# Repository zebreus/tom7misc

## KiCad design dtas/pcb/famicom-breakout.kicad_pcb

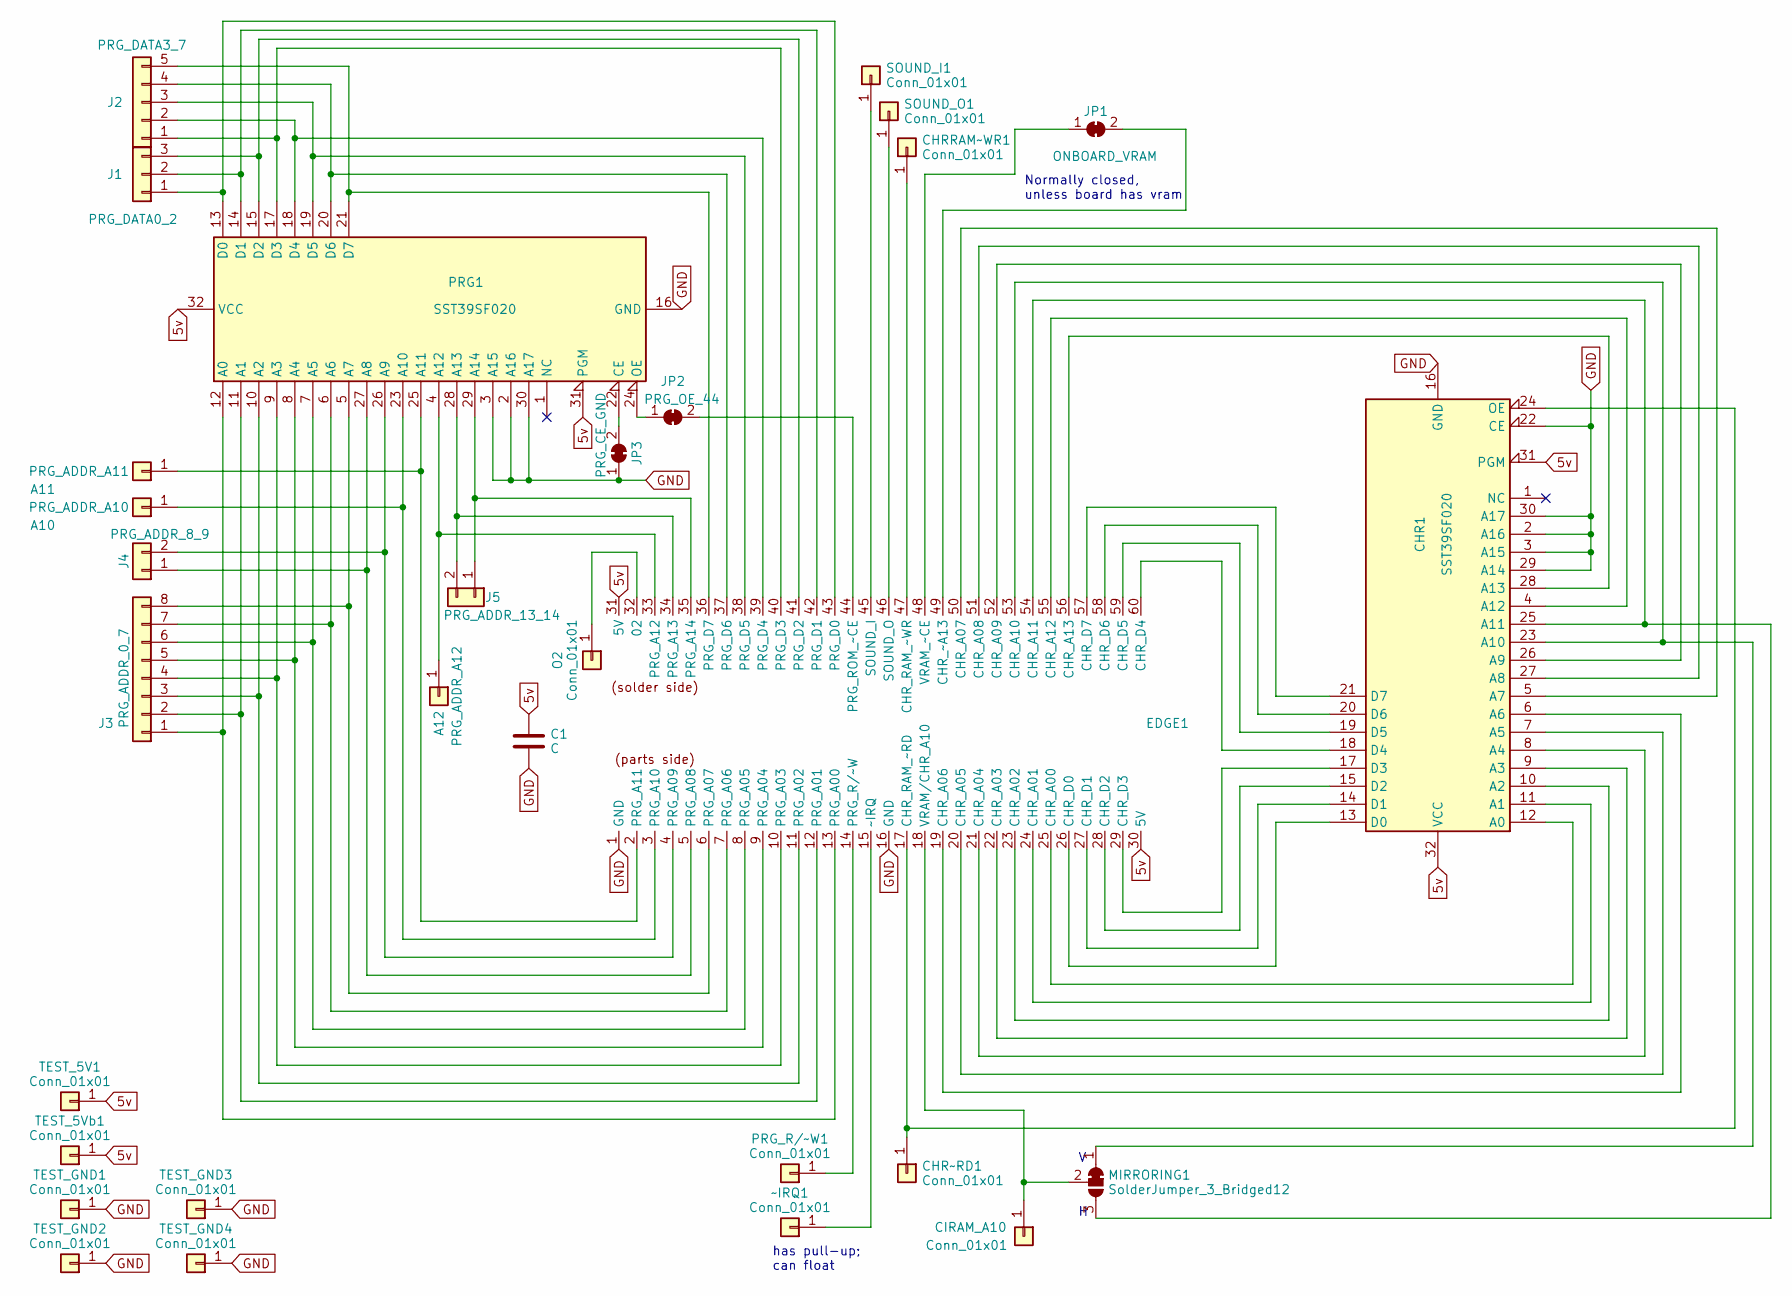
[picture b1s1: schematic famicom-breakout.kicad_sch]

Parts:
A10: PRG_ADDR_A10; PinHeader_1x01_P2.54mm_Vertical
A11: PRG_ADDR_A11; PinHeader_1x01_P2.54mm_Vertical
A12: PRG_ADDR_A12; PinHeader_1x01_P2.54mm_Vertical
C1: C; C_Disc_D6.0mm_W4.4mm_P5.00mm
CHR1: SST39SF020; DIP-32_W15.24mm
CHRRAM~WR1: Conn_01x01; PinHeader_1x01_P2.54mm_Vertical
CHR~RD1: Conn_01x01; PinHeader_1x01_P2.54mm_Vertical
CIRAM_A10: Conn_01x01; PinHeader_1x01_P2.54mm_Vertical
EDGE1: famicartedge
J1: PRG_DATA0_2; PinHeader_1x03_P2.54mm_Vertical
J2: PRG_DATA3_7; PinHeader_1x05_P2.54mm_Vertical
J3: PRG_ADDR_0_7; PinHeader_1x08_P2.54mm_Vertical
J4: PRG_ADDR_8_9; PinHeader_1x02_P2.54mm_Vertical
J5: PRG_ADDR_13_14; PinHeader_1x02_P2.54mm_Vertical
JP1: ONBOARD_VRAM; testjumperclosed
JP2: PRG_OE_44; testjumperclosed
JP3: PRG_CE_GND; testjumperclosed
MIRRORING1: SolderJumper_3_Bridged12; SolderJumper-3_P1.3mm_Bridged12_RoundedPad1.0x1.5mm
O2: Conn_01x01; PinHeader_1x01_P2.54mm_Vertical
PRG1: SST39SF020; DIP-32_W15.24mm
PRG_R/~W1: Conn_01x01; PinHeader_1x01_P2.54mm_Vertical
SOUND_I1: Conn_01x01; PinHeader_1x01_P2.54mm_Vertical
SOUND_O1: Conn_01x01; PinHeader_1x01_P2.54mm_Vertical
TEST_5V1, TEST_5Vb1: Conn_01x01; PinHeader_1x01_P2.54mm_Vertical
TEST_GND1, TEST_GND2, TEST_GND3, TEST_GND4: Conn_01x01; PinHeader_1x01_P2.54mm_Vertical
~IRQ1: Conn_01x01; PinHeader_1x01_P2.54mm_Vertical

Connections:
5v: C1.1, CHR1.31 (PGM), CHR1.32 (VCC), EDGE1.30 (5V), EDGE1.31 (5V), PRG1.31 (PGM), PRG1.32 (VCC), TEST_5V1.1, TEST_5Vb1.1
GND: C1.2, CHR1.2 (A16), CHR1.3 (A15), CHR1.16 (GND), CHR1.22 (CE), CHR1.29 (A14), CHR1.30 (A17), EDGE1.1 (GND), EDGE1.16 (GND), JP3.1 (A), PRG1.2 (A16), PRG1.3 (A15), PRG1.16 (GND), PRG1.30 (A17), TEST_GND1.1, TEST_GND2.1, TEST_GND3.1, TEST_GND4.1
unnamed: A10.1, EDGE1.3 (PRG_A10), PRG1.23 (A10)
unnamed: A11.1, EDGE1.2 (PRG_A11), PRG1.25 (A11)
unnamed: A12.1, EDGE1.33 (PRG_A12), PRG1.4 (A12)
unnamed: CHR1.12 (A0), EDGE1.25 (CHR_A00)
unnamed: CHR1.11 (A1), EDGE1.24 (CHR_A01)
unnamed: CHR1.10 (A2), EDGE1.23 (CHR_A02)
unnamed: CHR1.9 (A3), EDGE1.22 (CHR_A03)
unnamed: CHR1.8 (A4), EDGE1.21 (CHR_A04)
unnamed: CHR1.7 (A5), EDGE1.20 (CHR_A05)
unnamed: CHR1.6 (A6), EDGE1.19 (CHR_A06)
unnamed: CHR1.5 (A7), EDGE1.50 (CHR_A07)
unnamed: CHR1.27 (A8), EDGE1.51 (CHR_A08)
unnamed: CHR1.26 (A9), EDGE1.52 (CHR_A09)
unnamed: CHR1.23 (A10), EDGE1.53 (CHR_A10), MIRRORING1.1 (A)
unnamed: CHR1.25 (A11), EDGE1.54 (CHR_A11), MIRRORING1.3 (B)
unnamed: CHR1.4 (A12), EDGE1.55 (CHR_A12)
unnamed: CHR1.28 (A13), EDGE1.56 (CHR_A13)
unnamed: CHR1.13 (D0), EDGE1.26 (CHR_D0)
unnamed: CHR1.14 (D1), EDGE1.27 (CHR_D1)
unnamed: CHR1.15 (D2), EDGE1.28 (CHR_D2)
unnamed: CHR1.17 (D3), EDGE1.29 (CHR_D3)
unnamed: CHR1.18 (D4), EDGE1.60 (CHR_D4)
unnamed: CHR1.19 (D5), EDGE1.59 (CHR_D5)
unnamed: CHR1.20 (D6), EDGE1.58 (CHR_D6)
unnamed: CHR1.21 (D7), EDGE1.57 (CHR_D7)
unnamed: CHR1.24 (OE), CHR~RD1.1, EDGE1.17 (CHR_RAM_~RD)
unnamed: CHRRAM~WR1.1, EDGE1.47 (CHR_RAM_~WR)
unnamed: CIRAM_A10.1, EDGE1.18 (VRAM/CHR_A10), MIRRORING1.2 (C)
unnamed: EDGE1.32 (02), O2.1
unnamed: EDGE1.49 (CHR_~A13), JP1.2 (B)
unnamed: EDGE1.13 (PRG_A00), J3.1, PRG1.12 (A0)
unnamed: EDGE1.12 (PRG_A01), J3.2, PRG1.11 (A1)
unnamed: EDGE1.11 (PRG_A02), J3.3, PRG1.10 (A2)
unnamed: EDGE1.10 (PRG_A03), J3.4, PRG1.9 (A3)
unnamed: EDGE1.9 (PRG_A04), J3.5, PRG1.8 (A4)
unnamed: EDGE1.8 (PRG_A05), J3.6, PRG1.7 (A5)
unnamed: EDGE1.7 (PRG_A06), J3.7, PRG1.6 (A6)
unnamed: EDGE1.6 (PRG_A07), J3.8, PRG1.5 (A7)
unnamed: EDGE1.5 (PRG_A08), J4.1, PRG1.27 (A8)
unnamed: EDGE1.4 (PRG_A09), J4.2, PRG1.26 (A9)
unnamed: EDGE1.34 (PRG_A13), J5.2, PRG1.28 (A13)
unnamed: EDGE1.35 (PRG_A14), J5.1, PRG1.29 (A14)
unnamed: EDGE1.43 (PRG_D0), J1.1, PRG1.13 (D0)
unnamed: EDGE1.42 (PRG_D1), J1.2, PRG1.14 (D1)
unnamed: EDGE1.41 (PRG_D2), J1.3, PRG1.15 (D2)
unnamed: EDGE1.40 (PRG_D3), J2.1, PRG1.17 (D3)
unnamed: EDGE1.39 (PRG_D4), J2.2, PRG1.18 (D4)
unnamed: EDGE1.38 (PRG_D5), J2.3, PRG1.19 (D5)
unnamed: EDGE1.37 (PRG_D6), J2.4, PRG1.20 (D6)
unnamed: EDGE1.36 (PRG_D7), J2.5, PRG1.21 (D7)
unnamed: EDGE1.44 (PRG_ROM_~CE), JP2.2 (B)
unnamed: EDGE1.14 (PRG_R/~W), PRG_R/~W1.1
unnamed: EDGE1.45 (SOUND_I), SOUND_I1.1
unnamed: EDGE1.46 (SOUND_O), SOUND_O1.1
unnamed: EDGE1.48 (VRAM_~CE), JP1.1 (A)
unnamed: EDGE1.15 (~IRQ), ~IRQ1.1
unnamed: JP2.1 (A), PRG1.24 (OE)
unnamed: JP3.2 (B), PRG1.22 (CE)

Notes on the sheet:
has pull-up; can float
Normally closed, unless board has vram

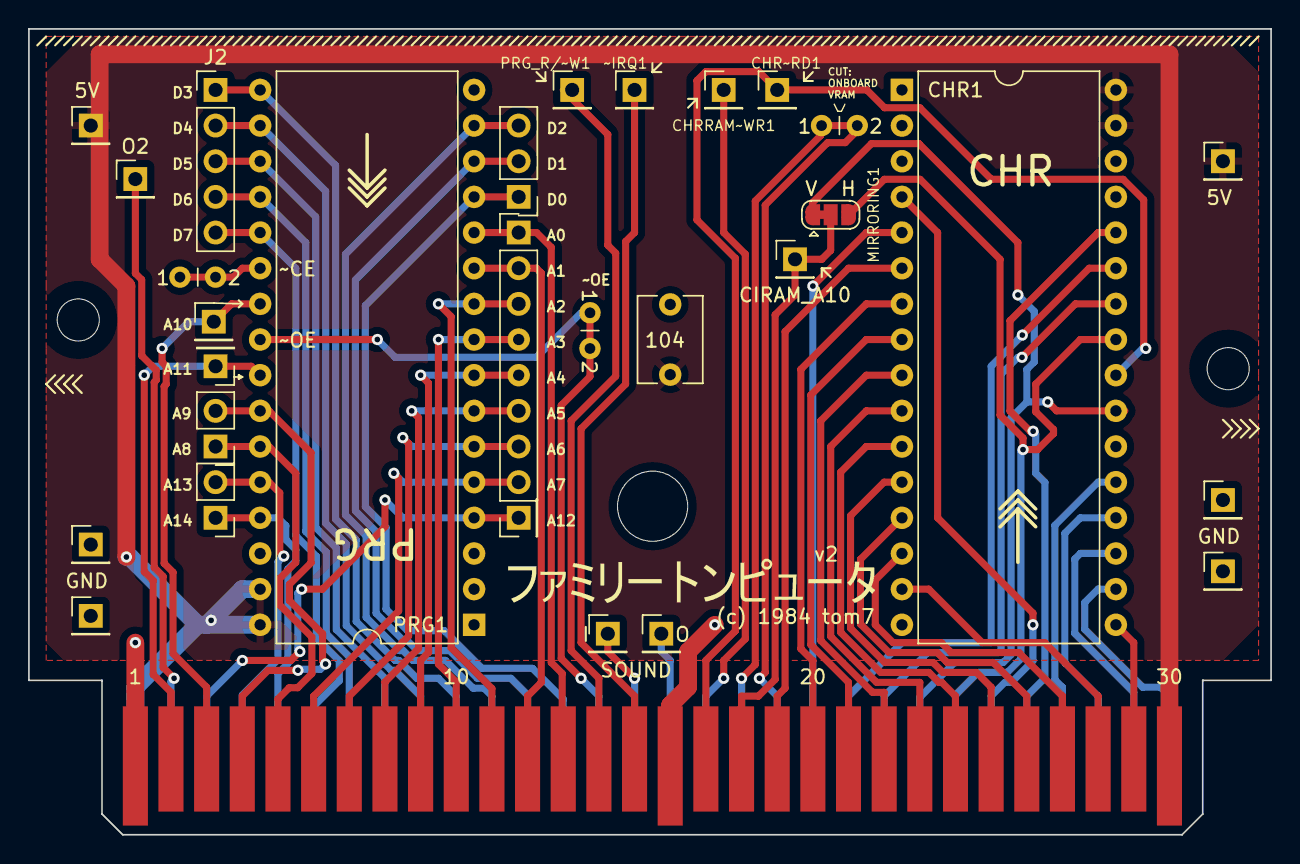
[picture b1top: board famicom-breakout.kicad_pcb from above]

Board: 2 copper layers, 88.5 x 57.4 mm, 29 parts (0 on the bottom side), 59 nets.

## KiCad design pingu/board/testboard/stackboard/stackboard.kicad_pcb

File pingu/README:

This is code (experimental, obviously) for several weird block devices
("hard drives"). See the video and paper at tom7.org/harder for an
introduction.

Note this whole thing is super insecure, for many reasons!
Don't run it on a system you care about!

 - unix domain socket has the wrong permissions

Compiling is something like this (from memory):
 - Get nbdkit (source) and compile it (in ../../nbdkit).
 - Install nbd-client too

make -j        (compile the .so plugins in this directory)
make -C viz    (compile the optional visualizations)

Modify run.sh to select the plugin you want, and the size.
sudo ./run.sh

You can then run
sudo ./benchmark.exe /mnt/[somedrive] file
to execute the simple benchmark.

# drop disk caches
sync && echo 3 | sudo tee /proc/sys/vm/drop_caches

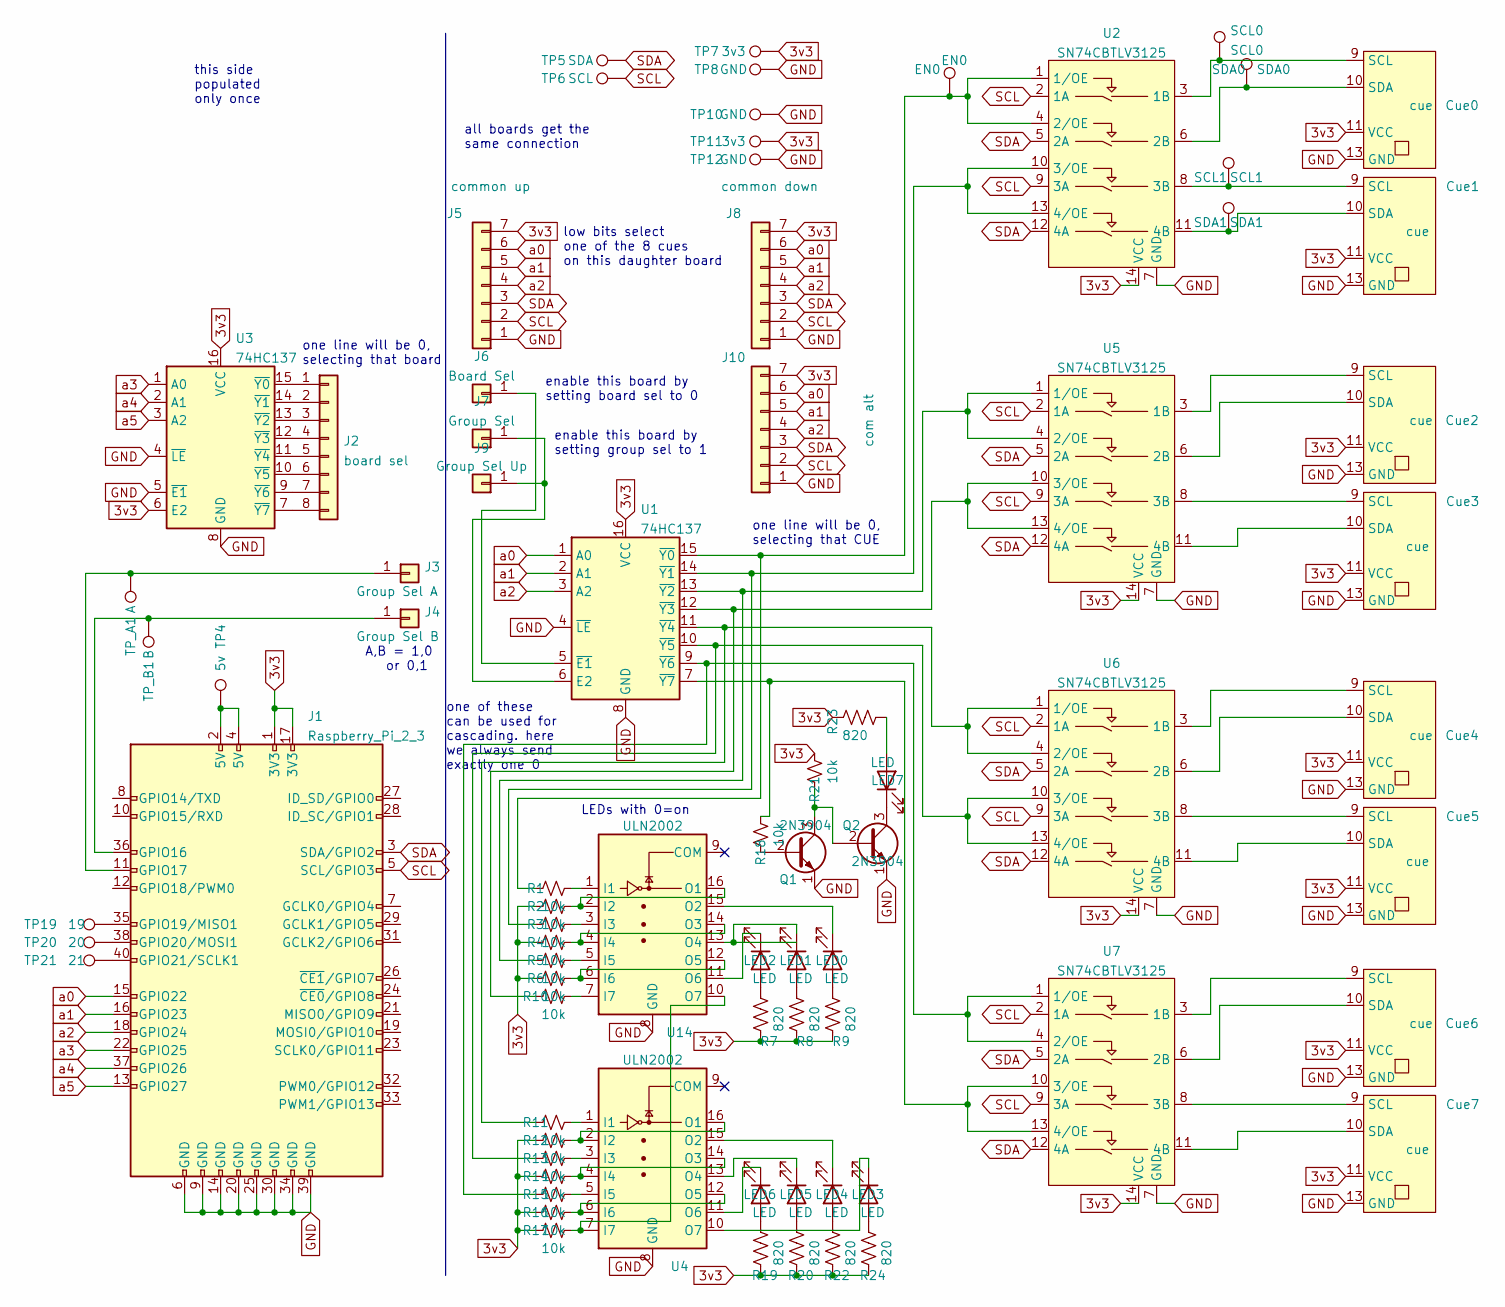
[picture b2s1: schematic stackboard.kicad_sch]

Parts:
Cue0, Cue1, Cue2, Cue3, Cue4, Cue5, Cue6, Cue7: cue; cuecastle
EN0: EN0; PinHeader_1x01_P2.54mm_Vertical
J1: Raspberry_Pi_2_3; PinHeader_2x20_P2.54mm_Vertical
J2: board sel; PinHeader_1x08_P2.54mm_Vertical
J3: Group Sel A; PinHeader_1x01_P2.54mm_Vertical
J4: Group Sel B; PinHeader_1x01_P2.54mm_Vertical
J5: common up; PinHeader_1x07_P2.54mm_Vertical
J6: Board Sel; PinHeader_1x01_P2.54mm_Vertical
J7: Group Sel; PinHeader_1x01_P2.54mm_Vertical
J8: common down; PinHeader_1x07_P2.54mm_Vertical
J9: Group Sel Up; PinHeader_1x01_P2.54mm_Vertical
J10: com alt; PinHeader_1x07_P2.54mm_Vertical
LED0, LED1, LED2, LED3, LED4, LED5, LED6, LED7: LED; LED_D2.0mm_W4.0mm_H2.8mm_FlatTop
Q1, Q2: 2N3904; TO-92_Inline
R1, R2, R3, R4, R5, R6, R10, R11, R12, R13, R14, R15, R16, R17, R18, R21: 10k; R_Axial_DIN0204_L3.6mm_D1.6mm_P7.62mm_Horizontal
R7, R8, R9, R19, R20, R22, R23, R24: 820; R_Axial_DIN0207_L6.3mm_D2.5mm_P10.16mm_Horizontal
SCL0: SCL0; PinHeader_1x01_P2.54mm_Vertical
SCL1: SCL1; PinHeader_1x01_P2.54mm_Vertical
SDA0: SDA0; PinHeader_1x01_P2.54mm_Vertical
SDA1: SDA1; PinHeader_1x01_P2.54mm_Vertical
TP4: 5v; PinHeader_1x01_P2.54mm_Vertical
TP5: SDA; PinHeader_1x01_P2.54mm_Vertical
TP6: SCL; PinHeader_1x01_P2.54mm_Vertical
TP7, TP11: 3v3; PinHeader_1x01_P2.54mm_Vertical
TP8, TP10, TP12: GND; PinHeader_1x01_P2.54mm_Vertical
TP19: 19; PinHeader_1x01_P2.54mm_Vertical
TP20: 20; PinHeader_1x01_P2.54mm_Vertical
TP21: 21; PinHeader_1x01_P2.54mm_Vertical
TP_A1: A; PinHeader_1x01_P2.54mm_Vertical
TP_B1: B; PinHeader_1x01_P2.54mm_Vertical
U1, U3: 74HC137; DIP-16_W7.62mm
U2, U5, U6, U7: SN74CBTLV3125; SOIC-14_3.9x8.7mm_P1.27mm
U4, U14: ULN2002; DIP-16_W7.62mm

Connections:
3v3: Cue0.11 (VCC), Cue1.11 (VCC), Cue2.11 (VCC), Cue3.11 (VCC), Cue4.11 (VCC), Cue5.11 (VCC), Cue6.11 (VCC), Cue7.11 (VCC), J1.1 (3V3), J1.17 (3V3), J5.7, J8.7, J10.7, R2.1, R4.1, R6.1, R7.1, R8.1, R9.1, R12.1, R14.1, R16.1, R17.1, R19.1, R20.1, R21.2, R22.1, R23.1, R24.1, TP7.1, TP11.1, U1.16 (VCC), U2.14 (VCC), U3.6 (E2), U3.16 (VCC), U5.14 (VCC), U6.14 (VCC), U7.14 (VCC); also elsewhere on the board
GND: Cue0.13 (GND), Cue1.13 (GND), Cue2.13 (GND), Cue3.13 (GND), Cue4.13 (GND), Cue5.13 (GND), Cue6.13 (GND), Cue7.13 (GND), J1.6 (GND), J1.9 (GND), J1.14 (GND), J1.20 (GND), J1.25 (GND), J1.30 (GND), J1.34 (GND), J1.39 (GND), J5.1, J8.1, J10.1, Q1.1 (E), Q2.1 (E), TP8.1, TP10.1, TP12.1, U1.4 (~LE), U1.8 (GND), U2.7 (GND), U3.4 (~LE), U3.5 (~E1), U3.8 (GND), U4.8 (GND), U5.7 (GND), U6.7 (GND), U7.7 (GND), U14.8 (GND); also elsewhere on the board
unnamed: Cue0.9 (SCL), SCL0.1, U2.3 (1B)
unnamed: Cue0.10 (SDA), SDA0.1, U2.6 (2B)
unnamed: Cue1.9 (SCL), SCL1.1, U2.8 (3B)
unnamed: Cue1.10 (SDA), SDA1.1, U2.11 (4B)
unnamed: Cue2.9 (SCL), U5.3 (1B)
unnamed: Cue2.10 (SDA), U5.6 (2B)
unnamed: Cue3.9 (SCL), U5.8 (3B)
unnamed: Cue3.10 (SDA), U5.11 (4B)
unnamed: Cue4.9 (SCL), U6.3 (1B)
unnamed: Cue4.10 (SDA), U6.6 (2B)
unnamed: Cue5.9 (SCL), U6.8 (3B)
unnamed: Cue5.10 (SDA), U6.11 (4B)
unnamed: Cue6.9 (SCL), U7.3 (1B)
unnamed: Cue6.10 (SDA), U7.6 (2B)
unnamed: Cue7.9 (SCL), U7.8 (3B)
unnamed: Cue7.10 (SDA), U7.11 (4B)
unnamed: EN0.1, R1.1, U1.15 (~Y0), U2.1 (1/OE), U2.4 (2/OE)
unnamed 19: J1.2 (5V), J1.4 (5V), TP4.1; also elsewhere on the board
unnamed 20: J1.11 (GPIO17), J3.1, TP_A1.1; also elsewhere on the board
unnamed 21: J1.35 (GPIO19/MISO1), TP19.1; also elsewhere on the board
unnamed 22: J1.36 (GPIO16), J4.1, TP_B1.1; also elsewhere on the board
unnamed 23: J1.38 (GPIO20/MOSI1), TP20.1; also elsewhere on the board
unnamed 24: J1.40 (GPIO21/SCLK1), TP21.1; also elsewhere on the board
unnamed: J2.1, U3.15 (~Y0)
unnamed: J2.2, U3.14 (~Y1)
unnamed: J2.3, U3.13 (~Y2)
unnamed: J2.4, U3.12 (~Y3)
unnamed: J2.5, U3.11 (~Y4)
unnamed: J2.6, U3.10 (~Y5)
unnamed: J2.7, U3.9 (~Y6)
unnamed: J2.8, U3.7 (~Y7)
unnamed: J6.1, U1.5 (~E1)
unnamed: J7.1, J9.1, U1.6 (E2)
unnamed: LED0.1 (K), U14.15 (O2)
unnamed: LED0.2 (A), R9.2
unnamed: LED1.1 (K), U14.13 (O4)
unnamed: LED1.2 (A), R8.2
unnamed: LED2.1 (K), U14.11 (O6)
unnamed: LED2.2 (A), R7.2
unnamed: LED3.1 (K), U4.10 (O7)
unnamed: LED3.2 (A), R24.2
unnamed: LED4.1 (K), U4.15 (O2)
unnamed: LED4.2 (A), R22.2
unnamed: LED5.1 (K), U4.13 (O4)
unnamed: LED5.2 (A), R20.2
unnamed: LED6.1 (K), U4.11 (O6)
unnamed: LED6.2 (A), R19.2
unnamed: LED7.1 (K), Q2.3 (C)
unnamed: LED7.2 (A), R23.2
unnamed: Q1.2 (B), R18.1
unnamed: Q1.3 (C), Q2.2 (B), R21.1
unnamed: R1.2, U14.1 (I1)
unnamed: R2.2, U14.2 (I2), U14.16 (O1)
unnamed: R3.1, U1.14 (~Y1), U2.10 (3/OE), U2.13 (4/OE)
unnamed: R3.2, U14.3 (I3)
unnamed: R4.2, U14.4 (I4), U14.14 (O3)
unnamed: R5.1, U1.13 (~Y2), U5.1 (1/OE), U5.4 (2/OE)
unnamed: R5.2, U14.5 (I5)
unnamed: R6.2, U14.6 (I6), U14.12 (O5)
unnamed: R10.1, U1.12 (~Y3), U5.10 (3/OE), U5.13 (4/OE)
unnamed: R10.2, U14.7 (I7)
unnamed: R11.1, U1.11 (~Y4), U6.1 (1/OE), U6.4 (2/OE)
unnamed: R11.2, U4.1 (I1)
unnamed: R12.2, U4.2 (I2), U4.16 (O1)
unnamed: R13.1, U1.10 (~Y5), U6.10 (3/OE), U6.13 (4/OE)
unnamed: R13.2, U4.3 (I3)
unnamed: R14.2, U4.4 (I4), U4.14 (O3)
unnamed: R15.1, U1.9 (~Y6), U7.1 (1/OE), U7.4 (2/OE)
unnamed: R15.2, U4.5 (I5)
unnamed: R16.2, U4.6 (I6), U4.12 (O5)
unnamed: R17.2, U4.7 (I7), U14.10 (O7)
unnamed: R18.2, U1.7 (~Y7), U7.10 (3/OE), U7.13 (4/OE)
SCL: J1.5 (SCL/GPIO3), J5.2, J8.2, J10.2, TP6.1, U2.2 (1A), U2.9 (3A), U5.2 (1A), U5.9 (3A), U6.2 (1A), U6.9 (3A), U7.2 (1A), U7.9 (3A); also elsewhere on the board
SDA: J1.3 (SDA/GPIO2), J5.3, J8.3, J10.3, TP5.1, U2.5 (2A), U2.12 (4A), U5.5 (2A), U5.12 (4A), U6.5 (2A), U6.12 (4A), U7.5 (2A), U7.12 (4A); also elsewhere on the board
a0: J1.15 (GPIO22), J5.6, J8.6, J10.6, U1.1 (A0); also elsewhere on the board
a1: J1.16 (GPIO23), J5.5, J8.5, J10.5, U1.2 (A1); also elsewhere on the board
a2: J1.18 (GPIO24), J5.4, J8.4, J10.4, U1.3 (A2); also elsewhere on the board
a3: J1.22 (GPIO25), U3.1 (A0); also elsewhere on the board
a4: J1.37 (GPIO26), U3.2 (A1); also elsewhere on the board
a5: J1.13 (GPIO27), U3.3 (A2); also elsewhere on the board

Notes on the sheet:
all boards get the same connection
this side populated only once
one line will be 0, selecting that board
A,B = 1,0 or 0,1
one line will be 0, selecting that CUE
low bits select one of the 8 cues on this daughter board
one of these can be used for cascading. here we always send exactly one 0
LEDs with 0=on
enable this board by setting group sel to 1
enable this board by setting board sel to 0

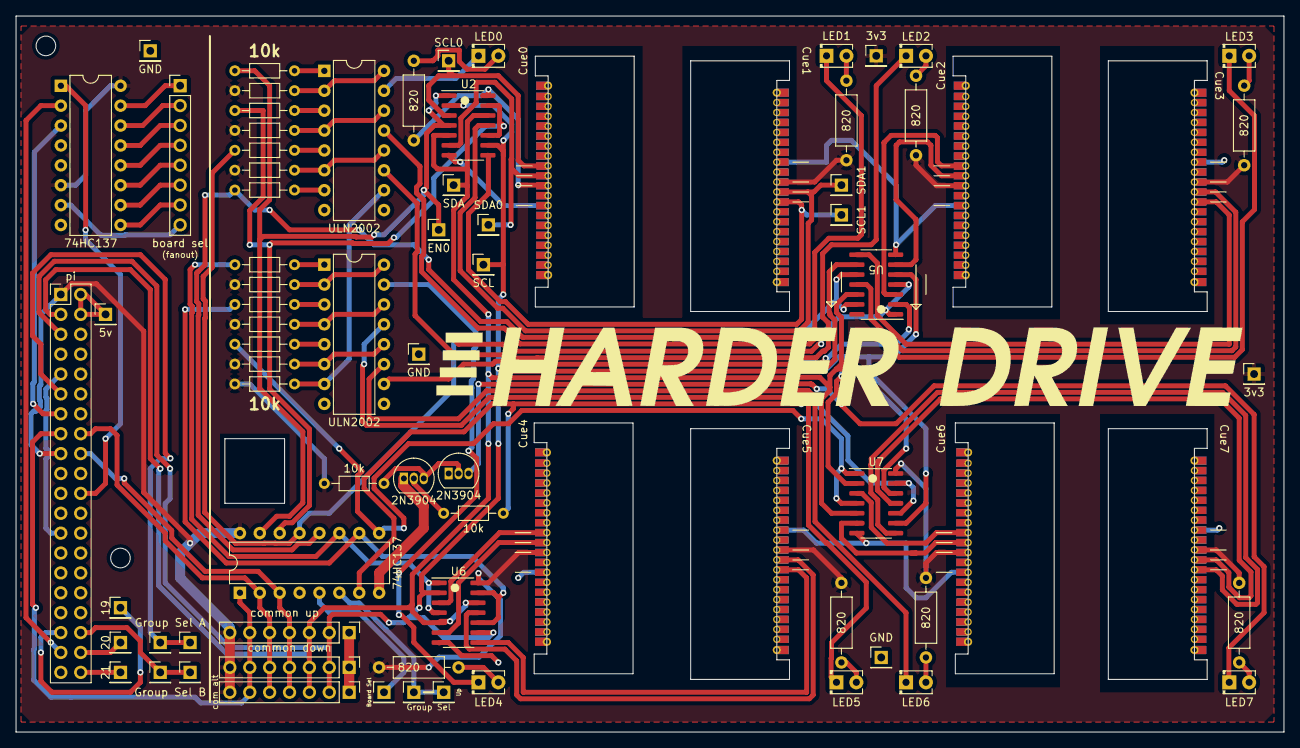
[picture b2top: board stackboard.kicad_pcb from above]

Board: 2 copper layers, 161.9 x 91.4 mm, 78 parts (0 on the bottom side), 82 nets.

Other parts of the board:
pi: Raspberry_Pi_2_3; PinHeader_2x20_P2.54mm_Vertical

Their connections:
3v3: pi.1 (3V3), pi.17 (3V3); also elsewhere on the board
GND: pi.6 (GND), pi.9 (GND), pi.14 (GND), pi.20 (GND), pi.25 (GND), pi.30 (GND), pi.34 (GND), pi.39 (GND); also elsewhere on the board
unnamed 19: pi.2 (5V), pi.4 (5V); also elsewhere on the board
unnamed 20: pi.11 (GPIO17); also elsewhere on the board
unnamed 21: pi.35 (GPIO19/MISO1); also elsewhere on the board
unnamed 22: pi.36 (GPIO16); also elsewhere on the board
unnamed 23: pi.38 (GPIO20/MOSI1); also elsewhere on the board
unnamed 24: pi.40 (GPIO21/SCLK1); also elsewhere on the board
SCL: pi.5 (SCL/GPIO3); also elsewhere on the board
SDA: pi.3 (SDA/GPIO2); also elsewhere on the board
a0: pi.15 (GPIO22); also elsewhere on the board
a1: pi.16 (GPIO23); also elsewhere on the board
a2: pi.18 (GPIO24); also elsewhere on the board
a3: pi.22 (GPIO25); also elsewhere on the board
a4: pi.37 (GPIO26); also elsewhere on the board
a5: pi.13 (GPIO27); also elsewhere on the board

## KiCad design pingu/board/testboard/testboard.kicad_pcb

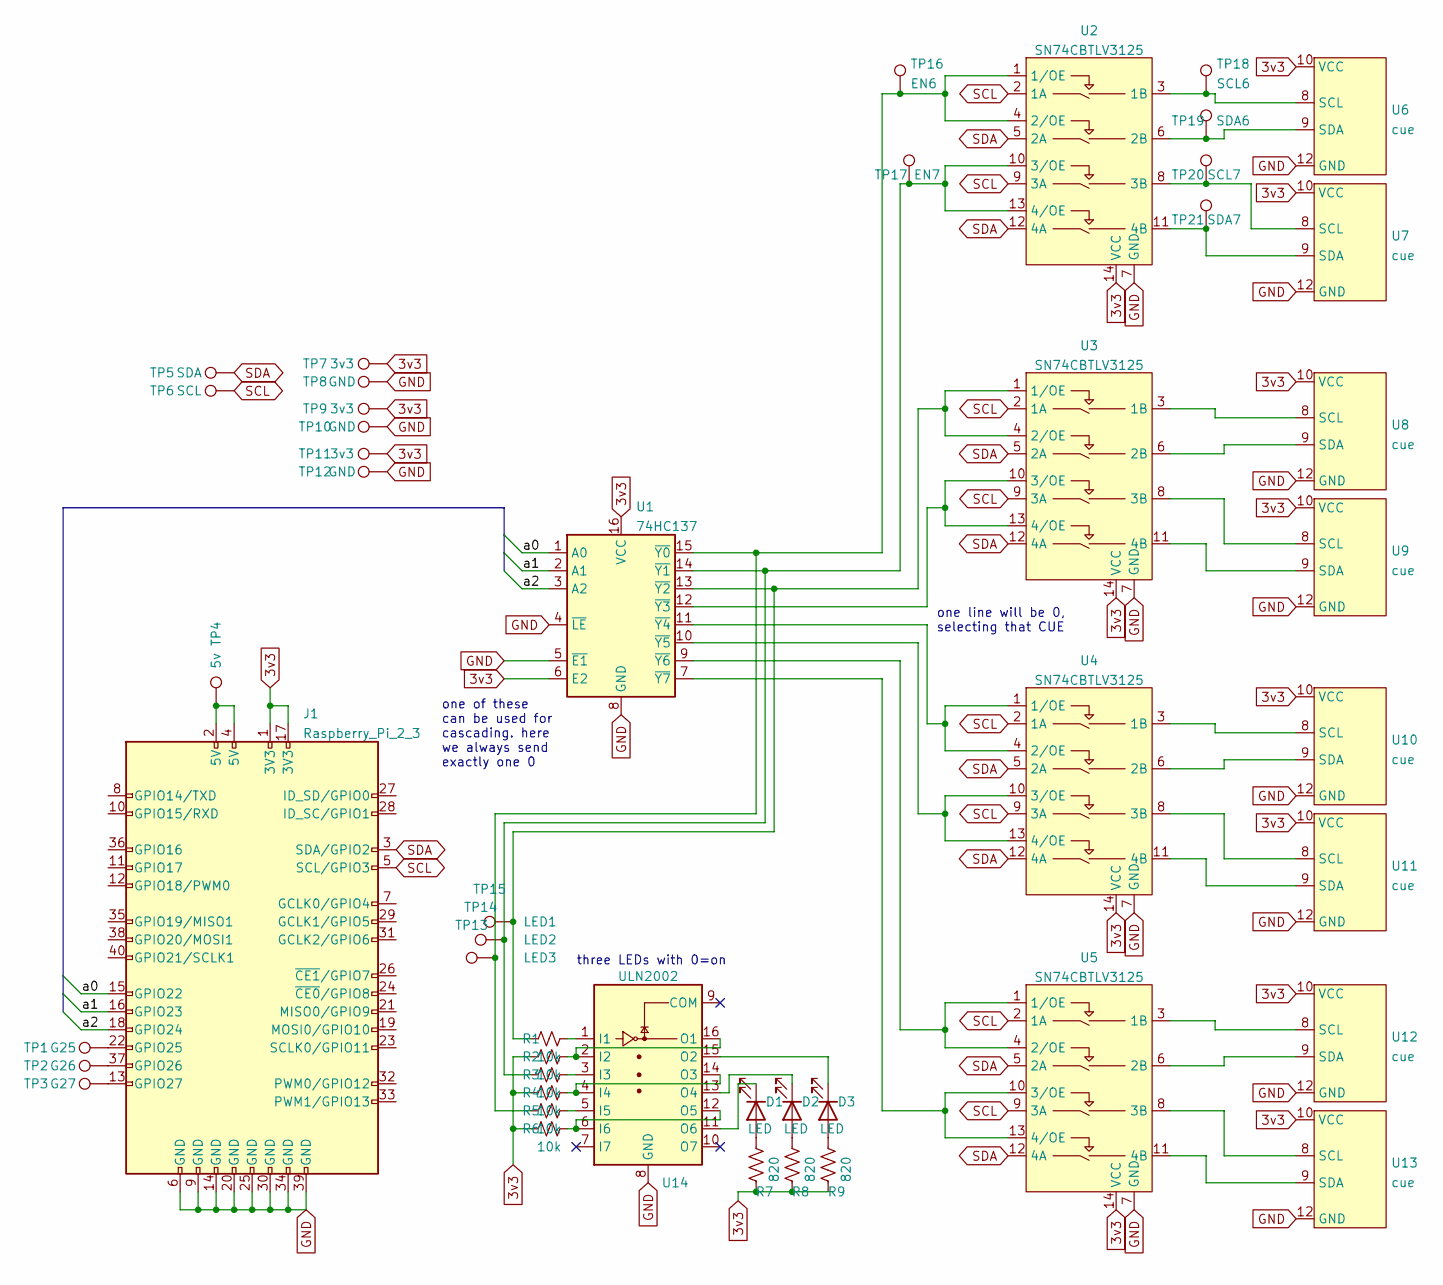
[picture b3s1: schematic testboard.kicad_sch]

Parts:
D1, D2, D3: LED; LED_D2.0mm_W4.0mm_H2.8mm_FlatTop
J1: Raspberry_Pi_2_3; PinHeader_2x20_P2.54mm_Vertical
R1, R2, R3, R4, R5, R6: 10k; R_Axial_DIN0207_L6.3mm_D2.5mm_P10.16mm_Horizontal
R7, R8, R9: 820; R_Axial_DIN0207_L6.3mm_D2.5mm_P10.16mm_Horizontal
TP1: G25; PinHeader_1x01_P2.54mm_Vertical
TP2: G26; PinHeader_1x01_P2.54mm_Vertical
TP3: G27; PinHeader_1x01_P2.54mm_Vertical
TP4: 5v; PinHeader_1x01_P2.54mm_Vertical
TP5: SDA; PinHeader_1x01_P2.54mm_Vertical
TP6: SCL; PinHeader_1x01_P2.54mm_Vertical
TP7, TP9, TP11: 3v3; PinHeader_1x01_P2.54mm_Vertical
TP8, TP10, TP12: GND; PinHeader_1x01_P2.54mm_Vertical
TP13: LED3; PinHeader_1x01_P2.54mm_Vertical
TP14: LED2; PinHeader_1x01_P2.54mm_Vertical
TP15: LED1; PinHeader_1x01_P2.54mm_Vertical
TP16: EN6; PinHeader_1x01_P2.54mm_Vertical
TP17: EN7; PinHeader_1x01_P2.54mm_Vertical
TP18: SCL6; PinHeader_1x01_P2.54mm_Vertical
TP19: SDA6; PinHeader_1x01_P2.54mm_Vertical
TP20: SCL7; PinHeader_1x01_P2.54mm_Vertical
TP21: SDA7; PinHeader_1x01_P2.54mm_Vertical
U1: 74HC137; DIP-16_W7.62mm
U2, U3, U4, U5: SN74CBTLV3125; SOIC-14_3.9x8.7mm_P1.27mm
U6, U12: cue; cuecastle-edge
U7, U8, U9, U10, U11, U13: cue; cuecastle
U14: ULN2002; DIP-16_W7.62mm

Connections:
3v3: J1.1 (3V3), J1.17 (3V3), R2.1, R4.1, R6.1, R7.1, R8.1, R9.1, TP7.1, TP9.1, TP11.1, U1.6 (E2), U1.16 (VCC), U2.14 (VCC), U3.14 (VCC), U4.14 (VCC), U5.14 (VCC), U6.10 (VCC), U7.10 (VCC), U8.10 (VCC), U9.10 (VCC), U10.10 (VCC), U11.10 (VCC), U12.10 (VCC), U13.10 (VCC)
/a0: J1.15 (GPIO22), U1.1 (A0)
/a1: J1.16 (GPIO23), U1.2 (A1)
/a2: J1.18 (GPIO24), U1.3 (A2)
GND: J1.6 (GND), J1.9 (GND), J1.14 (GND), J1.20 (GND), J1.25 (GND), J1.30 (GND), J1.34 (GND), J1.39 (GND), TP8.1, TP10.1, TP12.1, U1.4 (~LE), U1.5 (~E1), U1.8 (GND), U2.7 (GND), U3.7 (GND), U4.7 (GND), U5.7 (GND), U6.12 (GND), U7.12 (GND), U8.12 (GND), U9.12 (GND), U10.12 (GND), U11.12 (GND), U12.12 (GND), U13.12 (GND), U14.8 (GND)
unnamed: D1.1 (K), U14.11 (O6)
unnamed: D1.2 (A), R7.2
unnamed: D2.1 (K), U14.13 (O4)
unnamed: D2.2 (A), R8.2
unnamed: D3.1 (K), U14.15 (O2)
unnamed: D3.2 (A), R9.2
unnamed: J1.2 (5V), J1.4 (5V), TP4.1
unnamed: J1.13 (GPIO27), TP3.1
unnamed: J1.22 (GPIO25), TP1.1
unnamed: J1.37 (GPIO26), TP2.1
unnamed: R1.2, U14.1 (I1)
unnamed: R2.2, U14.2 (I2), U14.16 (O1)
unnamed: R3.2, U14.3 (I3)
unnamed: R4.2, U14.4 (I4), U14.14 (O3)
unnamed: R5.2, U14.5 (I5)
unnamed: R6.2, U14.6 (I6), U14.12 (O5)
unnamed: U1.7 (~Y7), U5.10 (3/OE), U5.13 (4/OE)
unnamed: U1.9 (~Y6), U5.1 (1/OE), U5.4 (2/OE)
unnamed: U1.10 (~Y5), U4.10 (3/OE), U4.13 (4/OE)
unnamed: U1.11 (~Y4), U4.1 (1/OE), U4.4 (2/OE)
unnamed: U1.12 (~Y3), U3.10 (3/OE), U3.13 (4/OE)
unnamed: R1.1, TP15.1, U1.13 (~Y2), U3.1 (1/OE), U3.4 (2/OE)
unnamed: R3.1, TP14.1, TP17.1, U1.14 (~Y1), U2.10 (3/OE), U2.13 (4/OE)
unnamed: R5.1, TP13.1, TP16.1, U1.15 (~Y0), U2.1 (1/OE), U2.4 (2/OE)
unnamed: TP18.1, U2.3 (1B), U6.8 (SCL)
unnamed: TP19.1, U2.6 (2B), U6.9 (SDA)
unnamed: TP20.1, U2.8 (3B), U7.8 (SCL)
unnamed: TP21.1, U2.11 (4B), U7.9 (SDA)
unnamed: U3.3 (1B), U8.8 (SCL)
unnamed: U3.6 (2B), U8.9 (SDA)
unnamed: U3.8 (3B), U9.8 (SCL)
unnamed: U3.11 (4B), U9.9 (SDA)
unnamed: U4.3 (1B), U10.8 (SCL)
unnamed: U4.6 (2B), U10.9 (SDA)
unnamed: U4.8 (3B), U11.8 (SCL)
unnamed: U4.11 (4B), U11.9 (SDA)
unnamed: U5.3 (1B), U12.8 (SCL)
unnamed: U5.6 (2B), U12.9 (SDA)
unnamed: U5.8 (3B), U13.8 (SCL)
unnamed: U5.11 (4B), U13.9 (SDA)
SCL: J1.5 (SCL/GPIO3), TP6.1, U2.2 (1A), U2.9 (3A), U3.2 (1A), U3.9 (3A), U4.2 (1A), U4.9 (3A), U5.2 (1A), U5.9 (3A)
SDA: J1.3 (SDA/GPIO2), TP5.1, U2.5 (2A), U2.12 (4A), U3.5 (2A), U3.12 (4A), U4.5 (2A), U4.12 (4A), U5.5 (2A), U5.12 (4A)

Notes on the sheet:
one line will be 0, selecting that CUE
one of these can be used for cascading. here we always send exactly one 0
three LEDs with 0=on

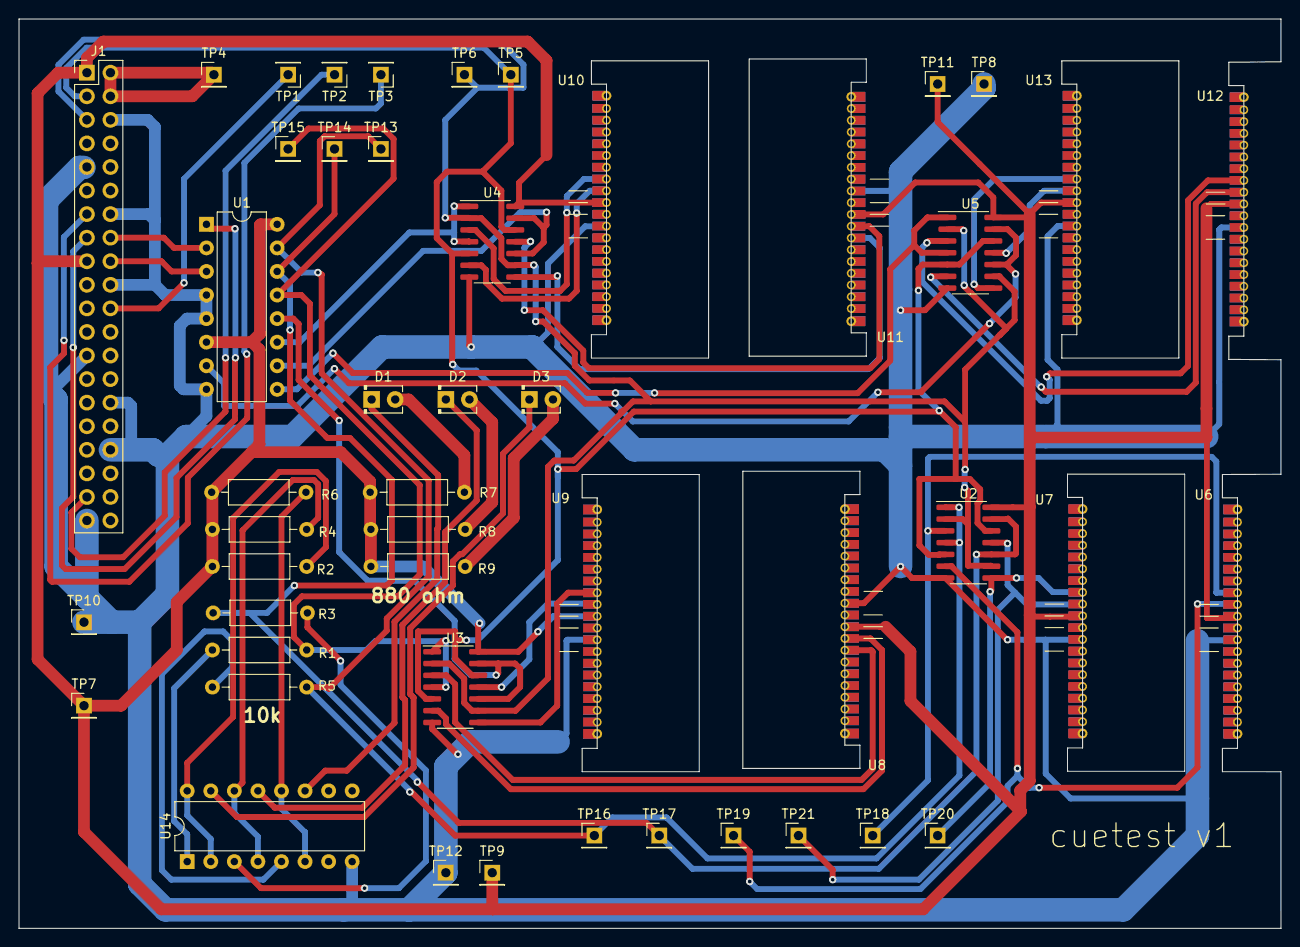
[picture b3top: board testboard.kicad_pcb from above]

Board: 2 copper layers, 136.0 x 98.0 mm, 48 parts (0 on the bottom side), 47 nets.

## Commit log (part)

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2026-06-06 Add highlighting to vertices/edges
2026-06-06 Multithreaded grind
2026-06-06 Add vertex constraint
2026-06-07 Tool to improve the geometry of hard instances
2026-06-08 Optimizer works now. These are almost certainly real counterexamples to the vertex conjecture
2026-06-08 Pull out the parameterization into a class so that there can be more than one.
2026-06-08 In 2026, it should just be in C++. Move old prototype to sml; add basic input and video.
2026-06-10 Box2D test
2026-06-10 Add triangulation routines from poly2tri
2026-06-10 Sync up a bunch of changes. Renamed Mesh2D so to make room for a more general Mesh2D type; fixed some compilation problems from code drift.
2026-06-11 Split out 2D polygon routines into their own file; fix some inconsistencies in the argument order etc.
2026-06-11 Remove famous executable bit from non-executable files (thanks cygwin?)
2026-06-12 Learned a new makefile trick for mixing headless/sdl builds in the directory. Let's see if I come to regret it. Added simple letter loader
2026-06-13 Clean up pdf and ttf code a little. We don't need the old, worse kerning table loop. codepoints should be uint32_t. Clean up polygons and polygonization a bit too
2026-06-13 Typing, kerning, map shift key smartly
2026-06-13 Refactor to move scene into its own file. Place on bottom of screen.
2026-06-14 Stress test parallelism. Seems you need to at least synchronize world creation and destruction.
2026-06-14 Split out P/R curve generation so that I can reuse font-db.
2026-06-14 Multimodal inputs (images)... not too bad
2026-06-14 Move fontdb to its own directory; I wanna use this for something else too
2026-06-15 Automatic classification works pretty well...
2026-06-15 Make TTF constructor fail gracefully. Make stb_truetype more tolerant of bad geometry. Can now make it through the SERIF fonts, at least.
2026-06-15 Move bezier stuff from lines.h to geom/bezier
2026-06-15 'editor' which actually just loads SVGs so I can use illustrator as editor
2026-06-17 Split out level code. separator to optimize
2026-06-17 Continue optimization
2026-06-17 This does find viable stuff, but I want to set the friction and restitution lower.
2026-06-18 Add the full ridiculous svg color list, since that keeps coming up (Illustrator will actually output some of these if they match). Add float sampling for pcg.h
2026-06-18 In working on the search, I just solved this manually.
2026-06-18 Check for empty contours when loading font; add fast mode
2026-06-18 Clean up makefile and add test coverage for missing ones
2026-06-19 Tricks to get the window to open in the foreground :sunglasses emoji:
2026-06-19 Cleanup; working on validation...
2026-06-19 100% validating AND and SEPARATOR.
2026-06-19 Current file should always be available. Try to reduce cases where it gives the filename instead of the full path.
2026-06-19 Add missing rendering.cc; more validation instances
2026-06-19 Split up validation so it can be used for optimization as well.
2026-06-20 Validating version of not. I did see some failures during optimization, so it might be worth a deeper look.
2026-06-20 Add sepxchng, which is easy. Start on props and chess to see how big the expression is (it's deceptively complex because of check-checks)
2026-06-21 OK, just need to check that non-king moves are not into (or remaining in) check, which is weirdly the hardest part...
2026-06-21 Commit before refactor
2026-06-21 Make chessprop stuff relative to a board. Fix many bugs. Add basic tests.
2026-06-21 Fix several more bugs. Could be correct now, except for the known corner case with ep.
2026-06-21 Fix a few more bugs :) And add simple simplifier
2026-06-22 Fix some more chess bugs. Standardize existing cells for layout.
2026-06-22 Standardize various cells; add some exchange variants
2026-06-22 Standardizing wires; start work on layout
2026-06-22 Really remove useless properties...
2026-06-22 Coffee shop progress
2026-06-22 Rename to circuit. Add Proposition equality.
2026-06-22 Tidy up the wires, add shape B
2026-06-23 Add dashed lines to GraphicsState in SVG parser, and fix some bugs relating to that. Misc other cleanup
2026-06-23 Oops, was missing simpledxf_test.cc. Fixed a bunch of issues with headers (missing include guards) while I'm at it.
2026-06-23 Clean up some. Make sure standard cells start at offset 0. Validation should assume standard cell layout (e.g. no input/output walls modeled).
2026-06-23 Add initializer_list constructor for InlineVector. Avoid zeroing out the reserved space in the constructor.
2026-06-24 Fix some bugs; validate from cells. Add separated not, which should be more reliable than the somewhat pesky mixed not.
2026-06-25 Add constant levels. Start on layout.
2026-06-25 Typed wires. Need combine gate too.
2026-06-26 Add separated NOT variants. Transform to and-normal form. Actually use cache...!
2026-06-26 Going to try this a different way...
2026-06-27 Some more standard cells, and maybe some progress on layout, which is turning out to be way hairier than I budgeted for :)
2026-06-27 First pass at layout...
2026-06-28 This is getting close, but tight wire geometry can get stuck due to some conservative settings...
2026-06-28 Fixed a silly issue where A and B wires variants were flipping two things at once. Now it almost works, but gets stuck on some tests because it's too crowded and it needs some non-local movement to m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
2026-06-28 Refactor some and expose methods for testing
2026-06-29 Modify some cells so that we have at least 16 blocks between inputs and outputs. It's too cramped otherwise, and we get stuck.
2026-06-29 It passes the (simple) layout tests now :)
2026-06-29 Clean this up a little.
2026-06-29 Reduce layout verbosity and give control
2026-06-29 What they always say: If it's getting hairy, add more hair
2026-06-29 Definitely getting there, but my big circuit is taking hours...
2026-06-30 Trying to shrink separators...
2026-06-30 This or gate does work, and is has a good joke in it. Need to fix a bug with space layers though.
2026-06-30 The 'modest' test passes again, with OR gates in the gamut

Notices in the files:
dtas/pcb/famicom-breakout.kicad_pcb:
(c) 1984 tom7
